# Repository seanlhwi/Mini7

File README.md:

# Mini7
A macro pad style custom drum pad with seven keys. This idea first reached me after yearning to try a drum set, but also wanted it to be portable. After pondering on what device type to use, I came across electronical drum pads, where each drum is practically a switch. It was at this moment when I thoguht about making the electronical drum set out of MX switches! Each of my keys are a different drum type, consisting of a base drum, high tom, mid tom, low tom, snare drum, hi-hat, and ride cymbal. Other key details are the battery monitoring screen and satisfying push button on/off button. The software was written on Aurduino IDE, and it is in a binary format to be flashed on a RP2040 Zero. Instead of just creating a box shape, the bottom two corners are cut to create a more interesting design. This project is easily recreatable by simply assemblying all of the parts according to the schematic and flashing the firmware. I hope to extend this drum system by making other types of drums too. 

# Mini7 Bill of Materials

| Name | Purpose | Quantity | Total (USD) | Link | Distributor |
|------|---------|----------|-------------|------|--------------|
| PCB | PCB | 5 | $10.40 | [View](https://cart.jlcpcb.com/shopcart/cart) | JLCPCB |
| Super Glue | Gluing | 1 | $2.72 | [View](https://www.aliexpress.us/item/3256808473825074.html) | Ali Express |
| MAX17048 Module | Battery monitor | 1 | $5.95 | [View](https://www.adafruit.com/product/5580) | Adafruit |
| Push Button | On/Off | 1 | $6.99 | [View](https://www.amazon.com/Cylewet-Self-Locking-Latching-Button-CYT1091/dp/B075VBV4QH) | Amazon |
| N52 Magnets | Securing Case | 10 | $2.56 | [View](https://www.aliexpress.us/item/3256810556183287.html) | Ali Express |
| 400mAh LiPo Battery | Battery | 1 | $8.99 | [View](https://www.amazon.com/Battery-Rechargeable-Lithium-Polymer-Connector/dp/B09F9W7Z6J) | Amazon |
| 0.91" OLED Screen | Battery Display | 2 | $5.99 | [View](https://www.amazon.com/Dorhea-Display-SSD1306-Arduino-3-3V-5V/dp/B07FMDB6TR) | Amazon |
| PCM5102A Module | Audio Output | 1 | $3.64 | [View](https://www.aliexpress.us/item/3256806642863761.html) | Ali Express |
| Tenstar RP2040 Zero | MCU | 2 | $5.19 | [View](https://www.aliexpress.us/item/3256806637247373.html) | Ali Express |
| TP4056 Module | Charging Unit | 1 | $1.39 | [View](https://www.aliexpress.us/item/3256808777213556.html) | Ali Express |
| 10 µF Capacitor | Capacitor | 50 | $3.10 | [View](https://www.aliexpress.us/item/3256807278239101.html) | Ali Express |
| 100nF Capacitor | Capacitor | 50 | $0.00 (Bundle) | [View](https://www.aliexpress.com/ssr/300001493/welcomegiftspmpc?productIds=1005007470747384) | Ali Express |
| 4.7k Resistors | Resistor | 1 | $2.88 | [View](https://www.aliexpress.com/ssr/300001493/welcomegiftspmpc?productIds=1005007470747384) | Ali Express |

## Totals

| Metric | Value |
|--------|-------|
| Total Number of Items | 13 |
| Total Number of Parts | 126 |
| **Total Cost** | **$59.80** |

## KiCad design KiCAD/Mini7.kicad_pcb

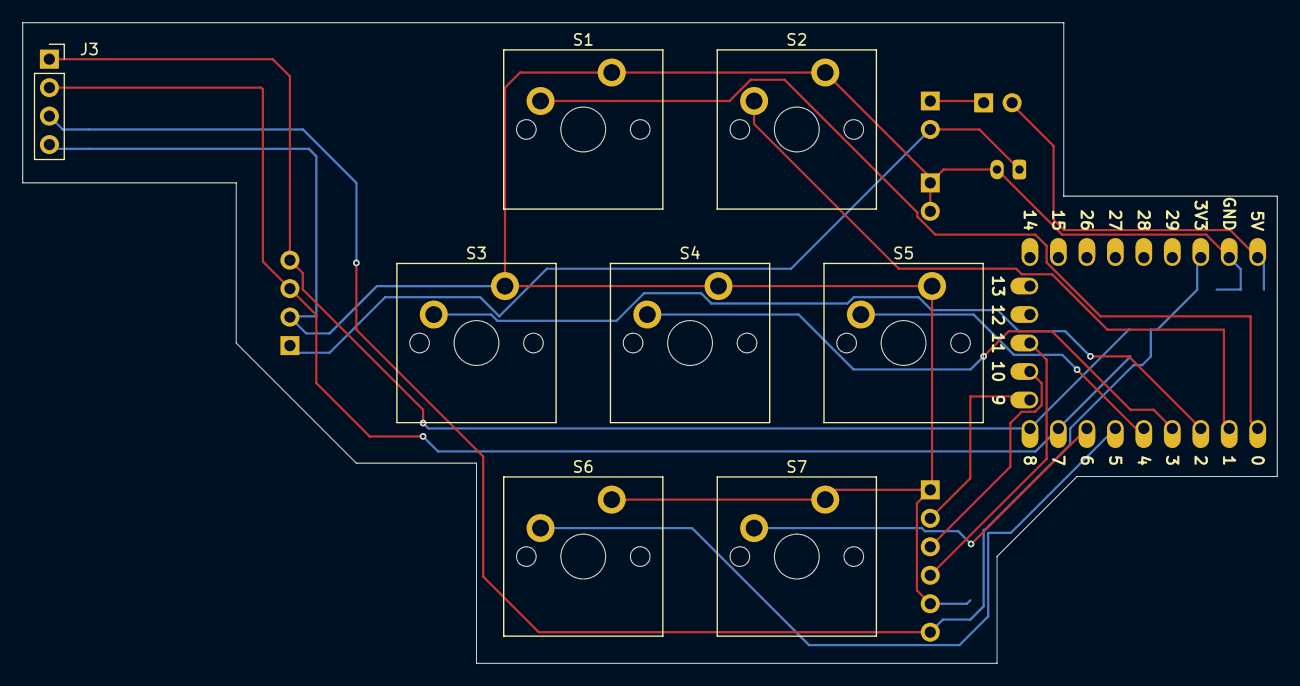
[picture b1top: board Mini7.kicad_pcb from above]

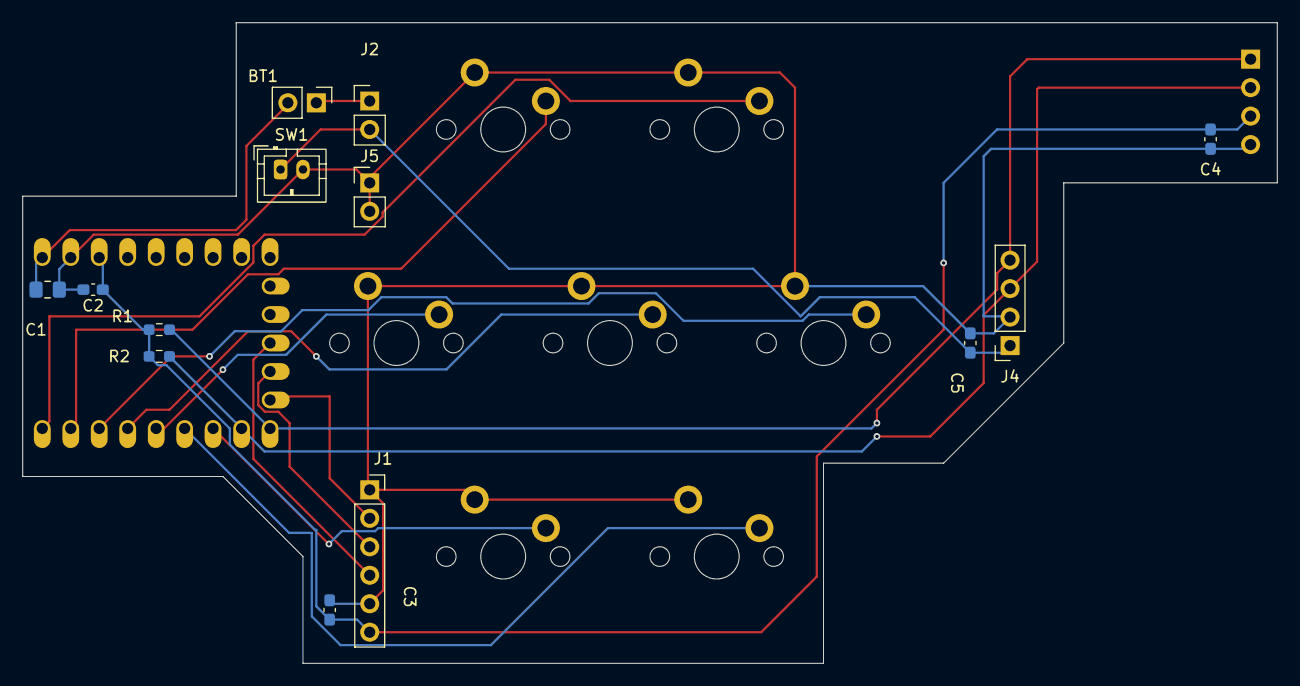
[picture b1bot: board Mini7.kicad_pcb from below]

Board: 2 copper layers, 111.9 x 57.1 mm, 22 parts (13 on the bottom side), 17 nets.

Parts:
BT1: LiPo; JST_PH_B2B-PH-K_1x02_P2.00mm_Vertical
C1: 10uF; C_0805_2012Metric_Pad1.18x1.45mm_HandSolder
C2, C3, C4, C5: 100nF; C_0603_1608Metric_Pad1.08x0.95mm_HandSolder
J1: PCM5102A; PinSocket_1x06_P2.54mm_Vertical
J2: TP4056 A; PinHeader_1x02_P2.54mm_Vertical
J3: OLED; PinSocket_1x04_P2.54mm_Vertical
J4: MAX17048; PinSocket_1x04_P2.54mm_Vertical
J5: TP4056 B; PinHeader_1x02_P2.54mm_Vertical
R1, R2: 4.7k; R_0603_1608Metric_Pad0.98x0.95mm_HandSolder
S1, S2, S3, S4, S5, S6, S7: MX_PCB_1.00u
SW1: Button; PinHeader_1x02_P2.54mm_Vertical
U1: RP2040_Zero

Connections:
+3V3: C2.1, C3.1, C4.1, J1.6 (VIN), J3.3 (VCC), R1.1, R2.1, U1.21 (3V3)
+BV: BT1.1 (Positive), C5.1, J2.2 (B+), J4.1 (VIN)
+SV: J2.1 (OUT+), SW1.1 (+SV)
+SWV: C1.1, SW1.2 (+SWV), U1.23 (5V)
GND: BT1.2 (Negative), C1.2, C2.2, C3.2, C4.2, C5.2, J1.1 (SCK), J1.5 (GND), J3.4 (GND), J4.2 (GND), J5.1 (B-), J5.2 (OUT-), S1.2, S2.2, S3.2, S4.2, S5.2, S6.2, S7.2, U1.22 (GND)
Pin10: J1.2 (BCK), U1.10 (9)
Pin11: J1.3 (DIN), U1.11 (10)
Pin12: J1.4 (LCK), U1.12 (11)
S1: S1.1, U1.1 (0)
S2: S2.1, U1.2 (1)
S3: S3.1, U1.3 (2)
S4: S4.1, U1.4 (3)
S5: S5.1, U1.5 (4)
S6: S6.1, U1.6 (5)
S7: S7.1, U1.7 (6)
SCL: J3.2 (SCL), J4.3 (SCL), R2.2, U1.8 (7)
SDA: J3.1 (SDA), J4.4 (SDA), R1.2, U1.9 (8)

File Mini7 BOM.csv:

Name,Purpose,Quantity,Total(USD),Link,Distributor
PCB,PCB,5,10.4,https://cart.jlcpcb.com/shopcart/cart,JLCPCB
Super Glue,Gluing,1,2.72,https://www.aliexpress.us/item/3256808473825074.html?spm=a2g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,Ali Express
MAX17048 Module,Battery monitor,1,5.95,https://www.adafruit.com/product/5580?srsltid=AfmBOooBtqFTi6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,Adafruit
Push Button,On/Off,1,6.99,https://www.amazon.com/Cylewet-Self-Locking-Latching-Button-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,Amazon
N52 Magnets,Securing Case,10,2.56,https://www.aliexpress.us/item/3256810556183287.html?spm=a2g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,Ali Express
400mAh LiPo Battery,Battery  ,1,8.99,https://www.amazon.com/Battery-Rechargeable-Lithium-Polymer-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,Amazon
"0.91"" Oled Screen",Battery Display,2,5.99,https://www.amazon.com/Dorhea-Display-SSD1306-Arduino-3-3V-5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,Amazon
PCM5102A Module,Audio Output,1,3.64,https://www.aliexpress.us/item/3256806642863761.html?spm=a2g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,Ali Express
Tenstar rp2040 Zero,MCU,2,5.19,https://www.aliexpress.us/item/3256806637247373.html?spm=a2g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,Ali Express
TP4056 Module,Charging Unit,1,1.39,https://www.aliexpress.us/item/3256808777213556.html?spm=a2g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,Ali Express
10 uF Capacitor,Capacitor,50,3.1,https://www.aliexpress.us/item/3256807278239101.html?spm=a2g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,Ali Express
100nF Capacitor,Capcitor,50,0.00 (Bundle),https://www.aliexpress.com/ssr/300001493/welcomegiftspmpc?sp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,Ali Express
4.7k Resistors,Resistor,1,2.88,https://www.aliexpress.com/ssr/300001493/welcomegiftspmpc?sp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,Ali Express
